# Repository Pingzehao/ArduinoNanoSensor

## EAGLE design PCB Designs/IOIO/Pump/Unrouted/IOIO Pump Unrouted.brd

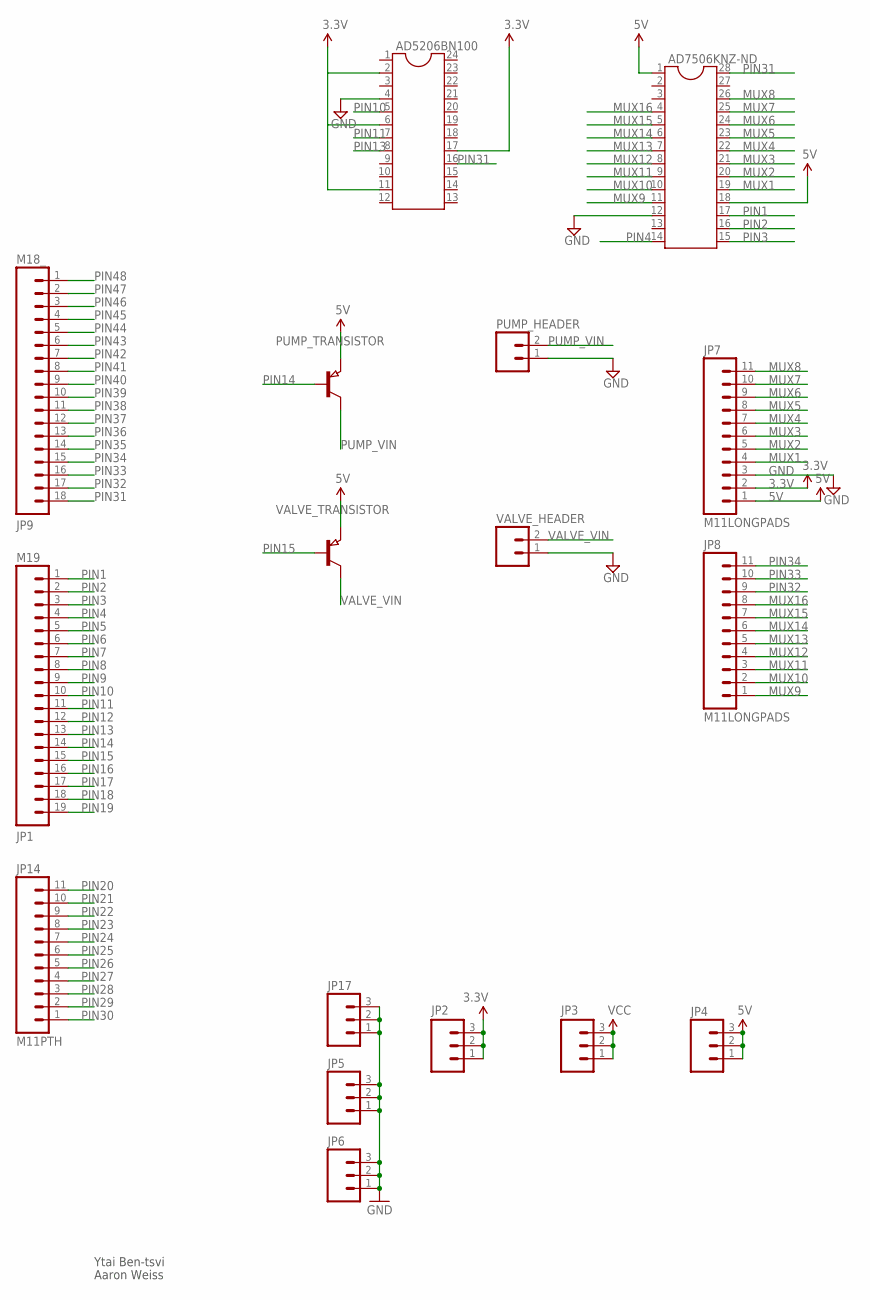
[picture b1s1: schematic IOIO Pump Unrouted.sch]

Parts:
AD5206BN100: DIL24-3
AD7506KNZ-ND: DIL28; DIL28-6
JP1: M19; 1X19
JP2, JP3, JP4, JP5, JP6, JP17: M03PTH; 1X03
JP7, JP8: M11LONGPADS; 1X11_LONGPADS
JP9: M18_; 1X18
JP14: M11PTH; 1X11
PUMP_HEADER: M02PTH; 1X02
PUMP_TRANSISTOR: PNP-TRANSISTOR_SOT23; SOT23
VALVE_HEADER: M02PTH; 1X02
VALVE_TRANSISTOR: PNP-TRANSISTOR_SOT23; SOT23

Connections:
3.3V: AD5206BN100.2, AD5206BN100.6, AD5206BN100.11, AD5206BN100.17, JP2.1, JP2.2, JP2.3, JP7.2
5V: AD7506KNZ-ND.1, AD7506KNZ-ND.18, JP4.1, JP4.2, JP4.3, JP7.1, PUMP_TRANSISTOR.2 (E), VALVE_TRANSISTOR.2 (E)
GND: AD5206BN100.4, AD7506KNZ-ND.12, JP5.1, JP5.2, JP5.3, JP6.1, JP6.2, JP6.3, JP7.3, JP17.1, JP17.2, JP17.3, PUMP_HEADER.1, VALVE_HEADER.1
MUX1: AD7506KNZ-ND.19, JP7.4
MUX2: AD7506KNZ-ND.20, JP7.5
MUX3: AD7506KNZ-ND.21, JP7.6
MUX4: AD7506KNZ-ND.22, JP7.7
MUX5: AD7506KNZ-ND.23, JP7.8
MUX6: AD7506KNZ-ND.24, JP7.9
MUX7: AD7506KNZ-ND.25, JP7.10
MUX8: AD7506KNZ-ND.26, JP7.11
MUX9: AD7506KNZ-ND.11, JP8.1
MUX10: AD7506KNZ-ND.10, JP8.2
MUX11: AD7506KNZ-ND.9, JP8.3
MUX12: AD7506KNZ-ND.8, JP8.4
MUX13: AD7506KNZ-ND.7, JP8.5
MUX14: AD7506KNZ-ND.6, JP8.6
MUX15: AD7506KNZ-ND.5, JP8.7
MUX16: AD7506KNZ-ND.4, JP8.8
PIN1: AD7506KNZ-ND.17, JP1.1
PIN2: AD7506KNZ-ND.16, JP1.2
PIN3: AD7506KNZ-ND.15, JP1.3
PIN4: AD7506KNZ-ND.14, JP1.4
PIN5: JP1.5
PIN6: JP1.6
PIN7: JP1.7
PIN8: JP1.8
PIN9: JP1.9
PIN10: AD5206BN100.5, JP1.10
PIN11: AD5206BN100.7, JP1.11
PIN12: JP1.12
PIN13: AD5206BN100.8, JP1.13
PIN14: JP1.14, PUMP_TRANSISTOR.1 (B)
PIN15: JP1.15, VALVE_TRANSISTOR.1 (B)
PIN16: JP1.16
PIN17: JP1.17
PIN18: JP1.18
PIN19: JP1.19
PIN20: JP14.11
PIN21: JP14.10
PIN22: JP14.9
PIN23: JP14.8
PIN24: JP14.7
PIN25: JP14.6
PIN26: JP14.5
PIN27: JP14.4
PIN28: JP14.3
PIN29: JP14.2
PIN30: JP14.1
PIN31: AD5206BN100.16, AD7506KNZ-ND.28, JP9.18
PIN32: JP8.9, JP9.17
PIN33: JP8.10, JP9.16
PIN34: JP8.11, JP9.15
PIN35: JP9.14
PIN36: JP9.13
PIN37: JP9.12
PIN38: JP9.11
PIN39: JP9.10
PIN40: JP9.9
PIN41: JP9.8
PIN42: JP9.7
PIN43: JP9.6
PIN44: JP9.5
PIN45: JP9.4
PIN46: JP9.3
PIN47: JP9.2
PIN48: JP9.1
PUMP_VIN: PUMP_HEADER.2, PUMP_TRANSISTOR.3 (C)
VALVE_VIN: VALVE_HEADER.2, VALVE_TRANSISTOR.3 (C)
VCC: JP3.1, JP3.2, JP3.3

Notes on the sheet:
Ytai Ben-tsvi
Aaron Weiss

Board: 2 copper layers, 17 parts (1 on the bottom side), 35 nets, no tracks yet.

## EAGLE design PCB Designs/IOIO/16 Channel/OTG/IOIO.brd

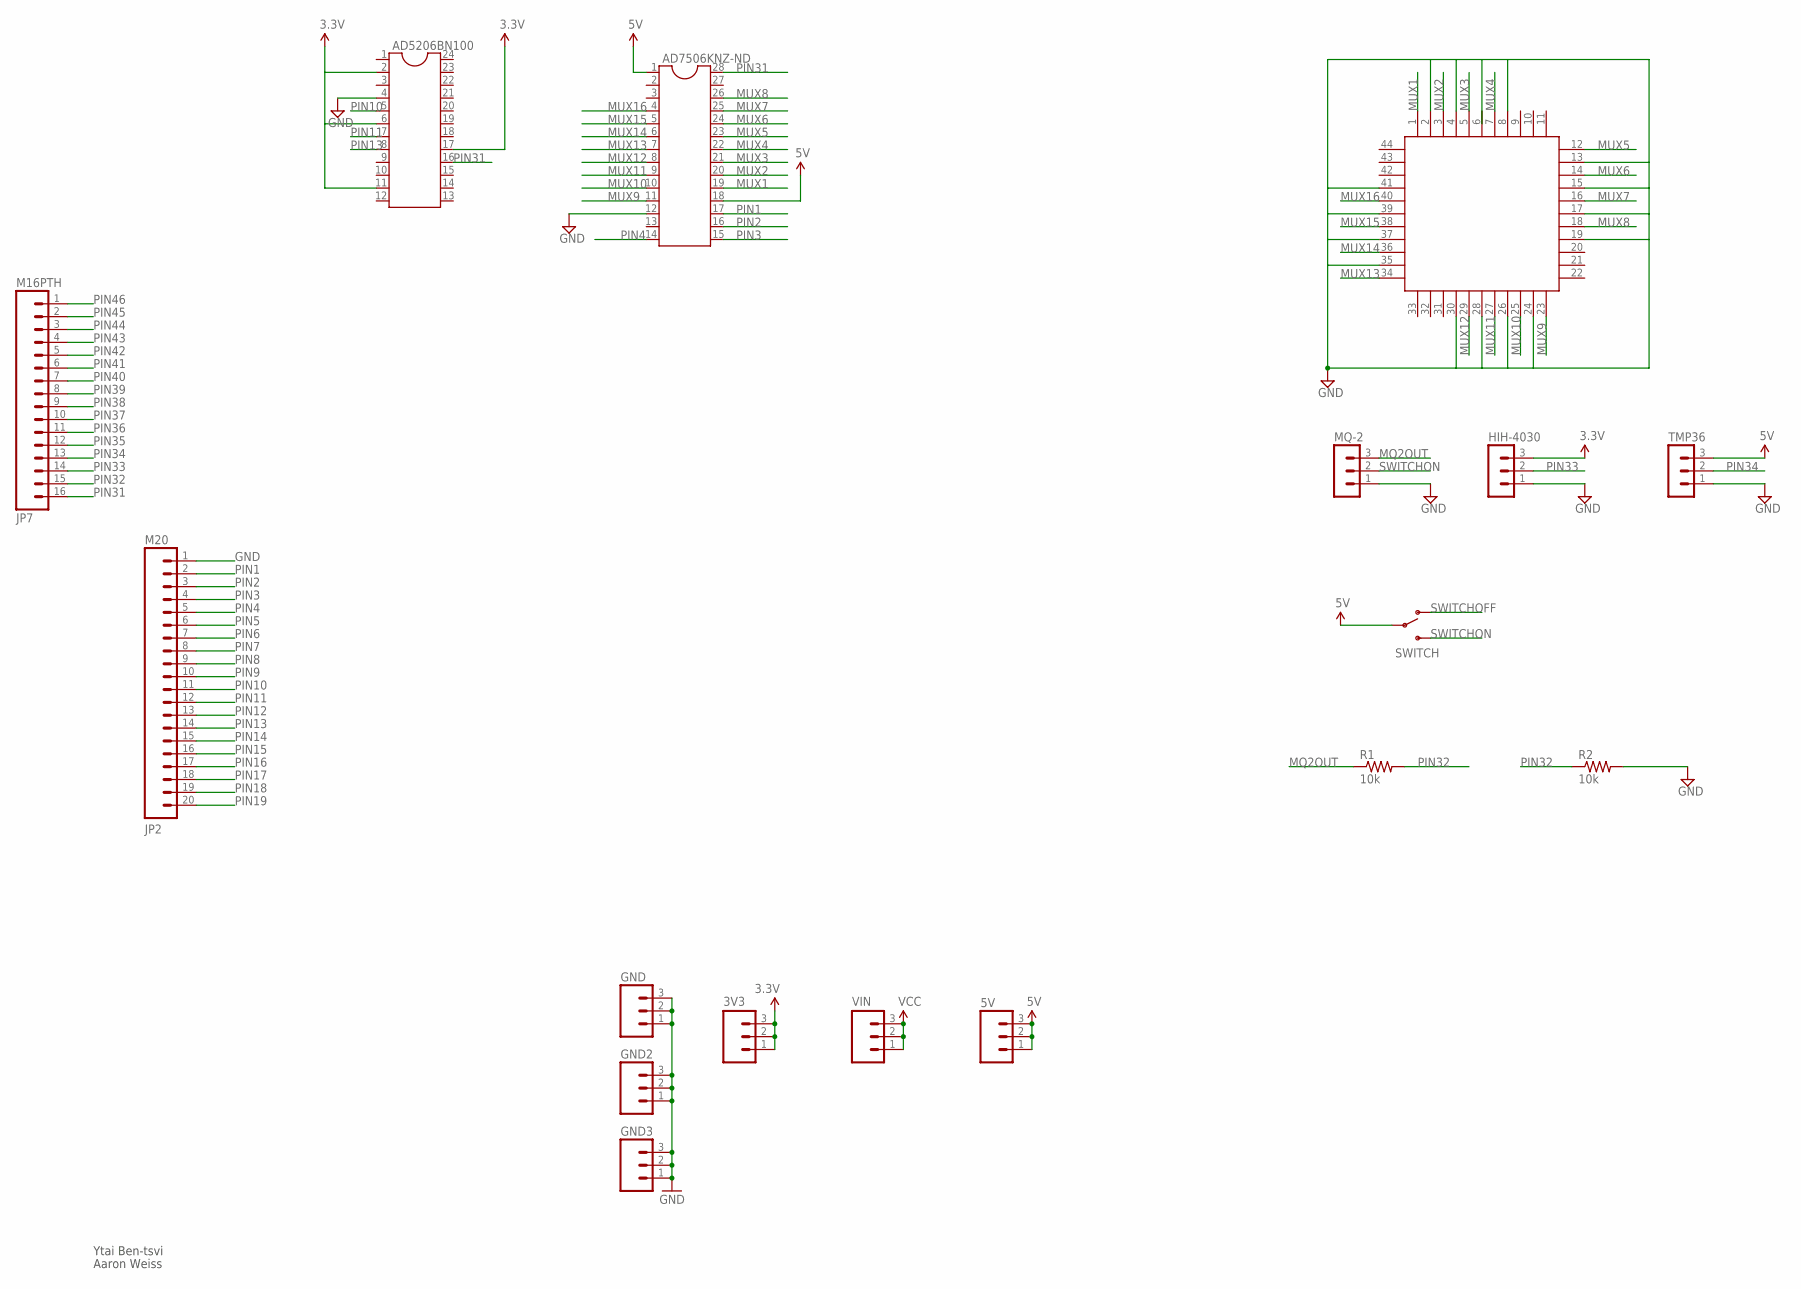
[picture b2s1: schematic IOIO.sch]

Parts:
3V3, 5V: M03PTH; 1X03
AD5206BN100: DIL24-3
AD7506KNZ-ND: DIL28; DIL28-6
GND, GND2, GND3: M03PTH; 1X03
HIH-4030: MA03-1
JP2: M20; 1X20
JP7: M16PTH; 1X16
MQ-2: MA03-1
R1, R2: 10k; 0207/7
SWITCH: SWITCH-SPSTPTH; SWITCH-SPDT
TMP36: MA03-1
U$1: S44
VIN: M03PTH; 1X03

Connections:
3.3V: 3V3.1, 3V3.2, 3V3.3, AD5206BN100.2, AD5206BN100.6, AD5206BN100.11, AD5206BN100.17, HIH-4030.3
5V: 5V.1, 5V.2, 5V.3, AD7506KNZ-ND.1, AD7506KNZ-ND.18, SWITCH.2, TMP36.3
GND: AD5206BN100.4, AD7506KNZ-ND.12, GND.1, GND.2, GND.3, GND2.1, GND2.2, GND2.3, GND3.1, GND3.2, GND3.3, HIH-4030.1, JP2.1, MQ-2.1, R2.2, TMP36.1, U$1.2, U$1.4, U$1.8, U$1.13, U$1.15, U$1.17, U$1.19, U$1.24, U$1.26, U$1.28, U$1.30, U$1.35, U$1.37, U$1.39, U$1.41
MQ2OUT: MQ-2.3, R1.1
MUX1: AD7506KNZ-ND.19, U$1.1
MUX2: AD7506KNZ-ND.20, U$1.3
MUX3: AD7506KNZ-ND.21, U$1.5
MUX4: AD7506KNZ-ND.22, U$1.7
MUX5: AD7506KNZ-ND.23, U$1.12
MUX6: AD7506KNZ-ND.24, U$1.14
MUX7: AD7506KNZ-ND.25, U$1.16
MUX8: AD7506KNZ-ND.26, U$1.18
MUX9: AD7506KNZ-ND.11, U$1.23
MUX10: AD7506KNZ-ND.10, U$1.25
MUX11: AD7506KNZ-ND.9, U$1.27
MUX12: AD7506KNZ-ND.8, U$1.29
MUX13: AD7506KNZ-ND.7, U$1.34
MUX14: AD7506KNZ-ND.6, U$1.36
MUX15: AD7506KNZ-ND.5, U$1.38
MUX16: AD7506KNZ-ND.4, U$1.40
PIN1: AD7506KNZ-ND.17, JP2.2
PIN2: AD7506KNZ-ND.16, JP2.3
PIN3: AD7506KNZ-ND.15, JP2.4
PIN4: AD7506KNZ-ND.14, JP2.5
PIN5: JP2.6
PIN6: JP2.7
PIN7: JP2.8
PIN8: JP2.9
PIN9: JP2.10
PIN10: AD5206BN100.5, JP2.11
PIN11: AD5206BN100.7, JP2.12
PIN12: JP2.13
PIN13: AD5206BN100.8, JP2.14
PIN14: JP2.15
PIN15: JP2.16
PIN16: JP2.17
PIN17: JP2.18
PIN18: JP2.19
PIN19: JP2.20
PIN31: AD5206BN100.16, AD7506KNZ-ND.28, JP7.16
PIN32: JP7.15, R1.2, R2.1
PIN33: HIH-4030.2, JP7.14
PIN34: JP7.13, TMP36.2
PIN35: JP7.12
PIN36: JP7.11
PIN37: JP7.10
PIN38: JP7.9
PIN39: JP7.8
PIN40: JP7.7
PIN41: JP7.6
PIN42: JP7.5
PIN43: JP7.4
PIN44: JP7.3
PIN45: JP7.2
PIN46: JP7.1
SWITCHOFF: SWITCH.1 (O)
SWITCHON: MQ-2.2, SWITCH.3 (S)
VCC: VIN.1, VIN.2, VIN.3

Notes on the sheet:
Ytai Ben-tsvi
Aaron Weiss

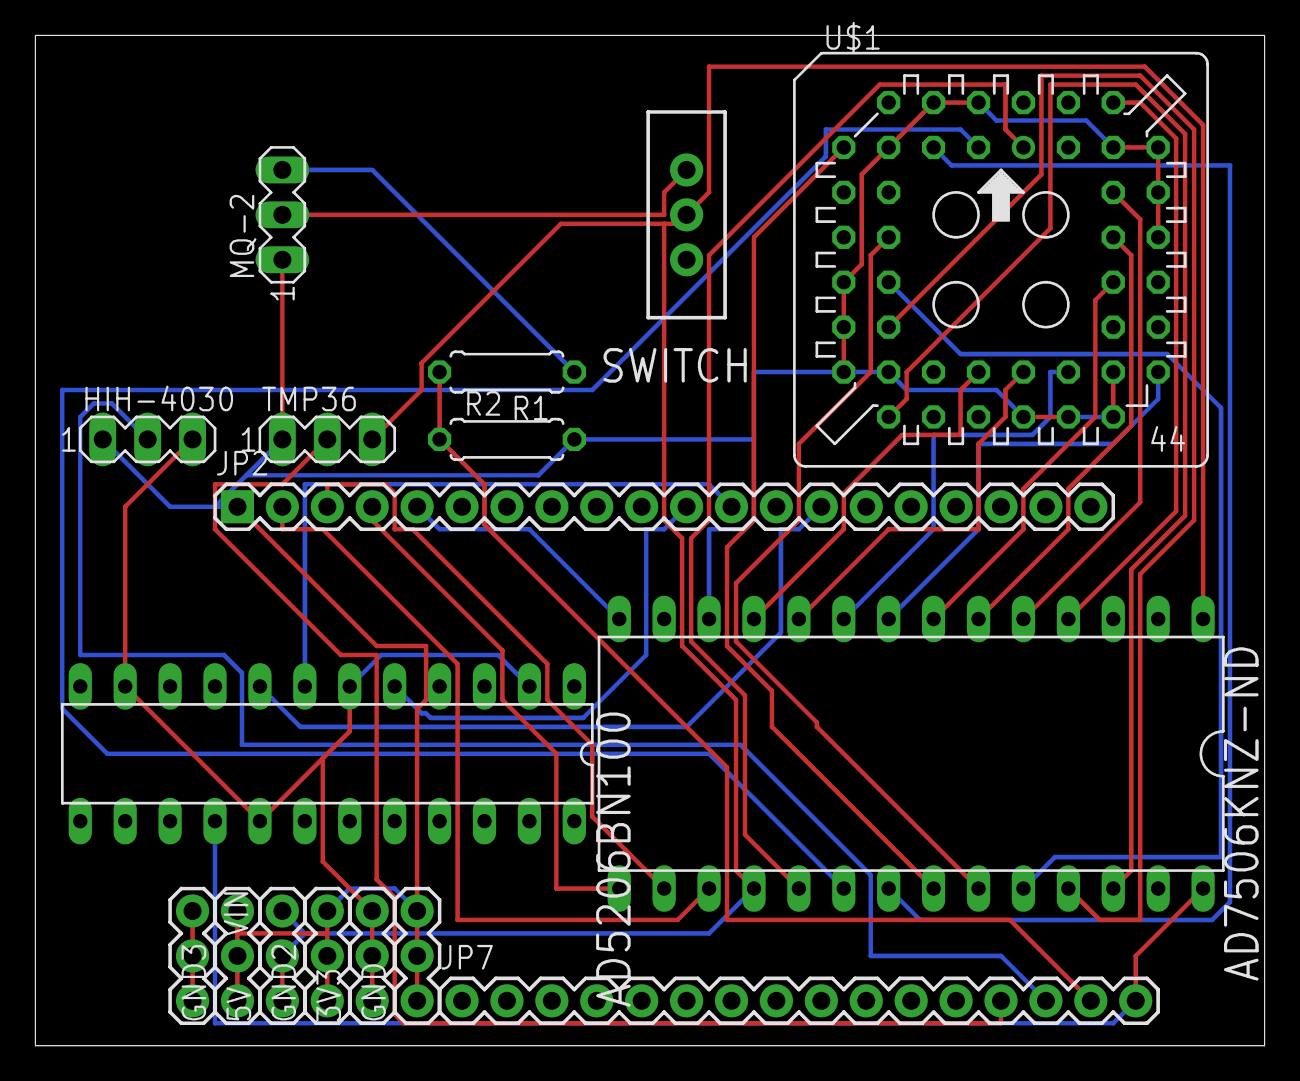
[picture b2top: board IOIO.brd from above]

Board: 2 copper layers, 69.5 x 57.1 mm, 17 parts (0 on the bottom side), 33 nets.

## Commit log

2013-09-30 Initial Upload
    Uploaded initial files to master branch.
2013-10-14 Added NanoSensorGrapher
    NanoSensorGrapher is a Java program that allows the selection of
    multiple data files to automatically process. It produces the graph
    output with normalized resistances as a png image file and a txt file
    with the max response at each concentration.

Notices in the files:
parts and their libraries:
SparkFun-Connectors: Licensing: CC v3.0 Share-Alike You are welcome to use this library for commercial purposes.
